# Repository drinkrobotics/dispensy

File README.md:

# Dispensy

One day aims to be a new hardware base for the [DrinkRobotics UbaBot](https://www.xythobuz.de/drinkrobotics.html).

Check out the [Dispensy documentation](https://drinkrobotics.github.io/dispensy/).

## License

This hardware of this project is licensed under the [CERN Open Hardware Licence Version 2 - Strongly Reciprocal (CERN-OHL-S-2.0+)](https://ohwr.org/cern_ohl_s_v2.txt) or any later version.
The SSD1306 footprint is from [KiCAD Rookie](https://kicadrookie.blogspot.com/2022/06/ssd1306-i2c-096in-oled-display-kicad_86.html).

The docs are built using [mdbook](https://github.com/rust-lang/mdBook), licensed as `MPL-2.0`.
The PCB SVG files in the documentation are displayed using [svg-pan-zoom](https://github.com/bumbu/svg-pan-zoom), licensed as `BSD-2-Clause`.
The 3D PCB files in the documentation are displayed using [three.js](hhttps://github.com/mrdoob/three.js), licensed as `MIT`.

Please also take a look at the `README.md` files in the subfolders of this project for more info.

     ------------------------------------------------------------------------------
    | Copyright (c) 2023 - 2024 Thomas Buck <thomas@xythobuz.de>                   |
    |                                                                              |
    | This source describes Open Hardware and is licensed under the CERN-OHL-S v2  |
    | or any later version.                                                        |
    |                                                                              |
    | You may redistribute and modify this source and make products using it under |
    | the terms of the CERN-OHL-S v2 (https://ohwr.org/cern_ohl_s_v2.txt)          |
    | or any later version.                                                        |
    |                                                                              |
    | This source is distributed WITHOUT ANY EXPRESS OR IMPLIED WARRANTY,          |
    | INCLUDING OF MERCHANTABILITY, SATISFACTORY QUALITY AND FITNESS FOR A         |
    | PARTICULAR PURPOSE. Please see the CERN-OHL-S v2 (or any later version)      |
    | for applicable conditions.                                                   |
    |                                                                              |
    | Source location: https://github.com/drinkrobotics/dispensy                   |
    |                                                                              |
    | As per CERN-OHL-S v2 section 4, should You produce hardware based on this    |
    | source, You must where practicable maintain the Source Location visible      |
    | on the external case of the Gizmo or other products you make using this      |
    | source.                                                                      |
     ------------------------------------------------------------------------------

The firmware of this project is licensed as GPLv3.
I initially adapted it from my own [Trackball](https://git.xythobuz.de/thomas/Trackball) and [Volcano Remote](https://git.xythobuz.de/thomas/sb-py) projects.
It uses the [Pi Pico SDK](https://github.com/raspberrypi/pico-sdk), licensed as BSD 3-clause, and therefore also [TinyUSB](https://github.com/hathach/tinyusb), licensed under the MIT license.
Some code is adapted from the TinyUSB examples.
To control the OLED display, [pico-ssd1306](https://github.com/daschr/pico-ssd1306) is used, licensed under the MIT license.
Repo metadata is embedded into the project using [cmake-git-version-tracking](https://github.com/andrew-hardin/cmake-git-version-tracking), licensed under the MIT license.

    This program is free software: you can redistribute it and/or modify
    it under the terms of the GNU General Public License as published by
    the Free Software Foundation, either version 3 of the License, or
    (at your option) any later version.

    This program is distributed in the hope that it will be useful,
    but WITHOUT ANY WARRANTY; without even the implied warranty of
    MERCHANTABILITY or FITNESS FOR A PARTICULAR PURPOSE.  See the
    GNU General Public License for more details.

    See <http://www.gnu.org/licenses/>.

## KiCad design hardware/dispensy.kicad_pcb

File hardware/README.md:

# Hardware

This is a KiCAD 8 hierarchical schematic and layout.
Take a look at the [docs](https://docs.kicad.org/7.0/en/eeschema/eeschema.html#hierarchical-schematics).

The repeated schematic sheets can also be replicated in the layout using [this plugin](https://github.com/MitjaNemec/ReplicateLayout).

To fetch symbols, footprints and 3d models automatically from [the JLCPCB parts library](https://jlcpcb.com/parts), [JLC2KiCad_lib](https://github.com/TousstNicolas/JLC2KiCad_lib) is used with the `fetch_jlc.sh` script.
To get the 3D models to have the correct offsets I used [this forked version](https://github.com/Xyntexx/JLC2KiCad_lib/tree/footprint_alignment_workarounds):

    pipx install git+https://github.com/Xyntexx/JLC2KiCad_lib.git@footprint_alignment_workarounds

In the future this may no longer be needed.

Gerber files and PDF and SVG plots can be generated using the included `generate_fab.sh` and `generate_plot.sh` scripts.

## External Libs

Uses SSD1306 footprint from [KiCAD Rookie](https://kicadrookie.blogspot.com/2022/06/ssd1306-i2c-096in-oled-display-kicad_86.html).

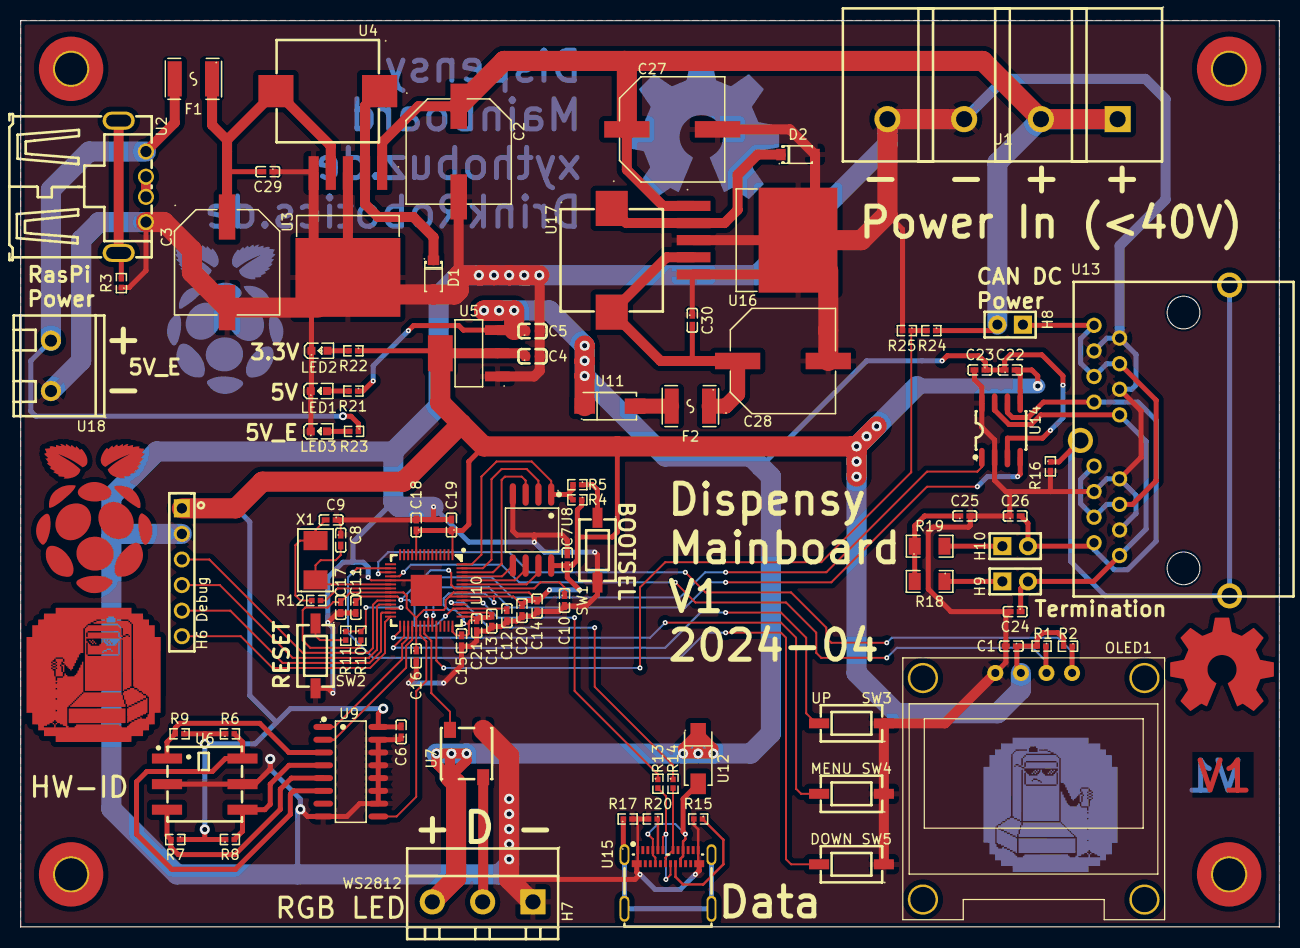
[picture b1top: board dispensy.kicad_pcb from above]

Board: 2 copper layers, 125.0 x 90.0 mm, 96 parts (0 on the bottom side), 64 nets.

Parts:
C1, C6, C7, C10, C11, C14, C15, C16, C17, C18, C19, C20, C21, C22, C29, C30: 100nF; C0402
C2, C27: 100uF; CAP-SMD_BD10.0-L10.3-W10.3-FD
C3, C28: 1000uF; CAP-SMD_BD10.0-L10.3-W10.3-LS11.3-FD
C4, C5: 10uF; C0603
C8, C9: 27p; C0402
C12, C13: 1uF; C0402
C23: 47nF; C0402
C24, C26: 100pF; C0402
C25: 4.7nF; C0402
D1, D2: MBR340F; SOD-123_L2.8-W1.8-LS3.7-RD
F1, F2: ASMD1812-350-16V; F1812
H6: Debug; HDR-TH_6P-P2.54-V-F
H7: WS2812; CONN-TH_XY300V-A-5.0-3P
H8: PWR; HDR-TH_2P-P2.54-V-M-1
H9: T_CH; HDR-TH_2P-P2.54-V-M-1
H10: T_CL; HDR-TH_2P-P2.54-V-M-1
H11, H12, H13, H14: MountingHole; MountingHole_3.2mm_M3_Pad_TopBottom
LED1, LED2, LED3: FC-D1608HGK-572C; LED0603-RD
OLED1: SSD1306; SSD1306_0.96_Oled
R1, R2, R4, R6, R7, R8, R9, R10, R25: 10K; R0402
R3, R16, R17: 1M; R0402
R5, R11, R12, R21, R22, R23: 1K; R0402
R13, R14: 27R4; R0402
R15, R20: 5K1; R0402
R18, R19: 60R4; R1206
R24: 147K; R0402
SW1: BOOTSEL; SW-SMD_L6.1-W3.6-LS6.6
SW2: RESET; SW-SMD_L6.1-W3.6-LS6.6
SW3: UP; SW-SMD_L6.1-W3.6-LS6.6
SW4: MENU; SW-SMD_L6.1-W3.6-LS6.6
SW5: DOWN; SW-SMD_L6.1-W3.6-LS6.6
U1: DBT50G-7_62-4P; CONN-TH_4P-P7.62_L15.2-W31.7-EX4.2
U2: USB-A; USB-A-TH_USB-302-T
U3, U16: LM2576S-5_0_TR; TO-263-5_L10.6-W9.6-P1.70-LS15.9-BR
U4, U17: 100uH; IND-SMD_L11.5-W10.0_YSPI1050
U5: AMS1117-3_3_C347222; SOT-223-4_L6.5-W3.5-P2.30-LS7.0-BR
U6: SKCR-16S; SW-SMD_SM_SKCR-16S
U7: WS2812E-V5; LED-SMD_4P-L5.0-W5.0-LS5.4-TL-1
U8: W25Q128JVSIQ; SOIC-8_L5.3-W5.3-P1.27-LS8.0-BL
U9: 74HC165D,653; SOIC-16_L9.9-W3.9-P1.27-LS6.0-BL
U10: RP2040; LQFN-56_L7.0-W7.0-P0.4-EP
U11, U12: SS54_C22452; SMA_L4.4-W2.8-LS5.4-R-RD
U13: CAN_IO; RJ45-TH_DS1129-05-S80BP-X
U14: TJA1042T_3_1J; SOIC-8_L5.0-W4.0-P1.27-LS6.0-BL
U15: USB-C; USB-C-SMD_TYPE-C-USB-18
U18: XY300V-A-5_0-2P; CONN-TH_XY300V-A-5.0-2P
X1: 12MHz; OSC-SMD_2P-L5.0-W3.2

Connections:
+1V1: C10.1, C11.1, C12.1, U10.23 (DVDD), U10.45 (VREG_VOUT), U10.50 (DVDD)
+3.3V: C1.1, C4.1, C6.2, C7.1, C13.1, C14.1, C15.1, C16.1, C17.1, C18.1, C19.1, C20.1, C21.1, C22.2, H6.1, OLED1.2 (VCC), R1.2, R2.2, R4.1, R6.1, R7.1, R8.1, R9.1, R10.2, R22.1, U5.2 (VOUT(TAB)), U5.4 (TAB), U8.8 (VCC), U9.16 (VCC), U10.1 (IOVDD), U10.10 (IOVDD), U10.22 (IOVDD), U10.33 (IOVDD), U10.42 (IOVDD), U10.43 (ADC_AVDD), U10.44 (VREG_IN), U10.48 (USB_VDD), U10.49 (IOVDD), U14.5 (VIO)
+5V: C5.1, C22.1, C23.1, H7.3, R21.1, U5.3 (VIN), U7.1 (VDD), U11.2 (K), U12.2 (K), U14.3 (VCC)
+VDC: C2.1, C27.1, H8.2, R24.1, U1.1, U1.2, U3.1 (VIN), U16.1 (VIN)
/EXT_PSU/Vout: C3.1, C29.2, F1.1, U3.4 (FB), U4.2
/PI/ADC0: R24.2, R25.1, U10.38 (GPIO26_ADC0)
/PI/Debug_Clock: H6.3, U10.24 (SWCLK)
/PI/Debug_Data: H6.4, U10.25 (SWD)
/PI/Debug_Rx: H6.6, U10.28 (GPIO17)
/PI/Debug_Tx: H6.5, U10.27 (GPIO16)
/PI/I2C_SCL: OLED1.3 (SCL), R1.1, U10.18 (GPIO15)
/PI/I2C_SDA: OLED1.4 (SDA), R2.1, U10.17 (GPIO14)
/PI/IO13: SW5.2, U10.16 (GPIO13)
/PI/IO14: SW4.2, U10.29 (GPIO18)
/PI/IO15: SW3.2, U10.30 (GPIO19)
/PI/LED_Din: U7.4 (DIN), U10.35 (GPIO23)
/PI/PI_PSU/Vout: C28.1, C30.2, F2.1, U16.4 (FB), U17.2
/PI/SPI_FLASH.SCLK: U8.6 (CLK), U10.52 (QSPI_SCLK)
/PI/SPI_FLASH.SD0: U8.5 (DI(IO0)), U10.53 (QSPI_SD0)
/PI/SPI_FLASH.SD1: U8.2 (DO(IO1)), U10.55 (QSPI_SD1)
/PI/SPI_FLASH.SD2: U8.3 (WP#(IO2)), U10.54 (QSPI_SD2)
/PI/SPI_FLASH.SD3: U8.7 (HOLD#orRESET#(IO3)), U10.51 (QSPI_SD3)
/PI/SPI_FLASH.SS: R4.2, R5.2, U8.1 (CS#), U10.56 (QSPI_SS)
/PI/SR_Clock: U9.2 (CP), U10.32 (GPIO21)
/PI/SR_Data: U9.9 (Q7), U10.34 (GPIO22)
/PI/SR_Load: U9.1 (PL#), U10.31 (GPIO20)
/PI/USBC.DM: R14.2, U15.A7 (D-), U15.B7 (D-)
/PI/USBC.DP: R13.2, U15.A6 (D+), U15.B6 (D+)
/PI/USBC.SHIELD: R17.1, U15.0
/PI/USBC.VBUS: U12.1 (A), U15.A4 (VBUS), U15.A9 (VBUS), U15.B4 (VBUS), U15.B9 (VBUS)
GND: C1.2, C2.2, C3.2, C4.2, C5.2, C6.1, C7.2, C8.1, C9.1, C10.2, C11.2, C12.2, C13.2, C14.2, C15.2, C16.2, C17.2, C18.2, C19.2, C20.2, C21.2, C23.2, C24.2, C25.2, C26.1, C27.2, C28.2, C29.1, C30.1, D1.2, D2.2, H6.2, H7.1, LED1.1 (-), LED2.1 (-), LED3.1 (-), OLED1.1 (GND), R3.1, R15.2, R16.2, R17.2, R20.2, R25.2, SW1.2, SW2.2, SW3.1, SW4.1, SW5.1, U1.3, U1.4, U2.4 (GND), U3.3 (GND), U3.5 (ON#/OFF), U3.6 (TAB), U5.1 (ADJ(GND)), U6.C1 (C), U6.C2 (C), U7.3 (GND), U8.4 (GND), U9.8 (GND), U9.10 (DS), U9.11 (D0), U9.12 (D1), U9.13 (D2), U9.14 (D3), U9.15 (CE#), U10.19 (TESTEN), U10.57 (GND), U13.3, U13.6, U13.7, U13.11, U13.14, U13.15, U14.2 (GND), U14.8 (STB), U15.A1 (GND), U15.A12 (GND), U15.B1 (GND), U15.B12 (GND), U16.3 (GND), U16.5 (ON#/OFF), U16.6 (TAB), U18.1
unnamed: C25.1, R18.2, R19.1
unnamed: H8.1, U13.4, U13.5, U13.8, U13.12, U13.13, U13.16
unnamed: H9.1, R18.1
unnamed: H10.1, R19.2
unnamed: LED1.2 (+), R21.2
unnamed: LED2.2 (+), R22.2
unnamed: LED3.2 (+), R23.2
unnamed: R5.1, SW1.1
unnamed: R11.2, SW2.1
unnamed: R16.1, U13.17, U13.18, U13.19
unnamed: U2.2 (D-), U2.3 (D+)
unnamed: R3.2, U2.5 (SH1), U2.6 (SH2)
unnamed: F1.2, R23.1, U2.1 (VCC), U18.2
unnamed: D1.1, U3.2 (OUT), U4.1
unnamed: H7.2, U7.2 (DO)
unnamed: R9.2, U6.1, U9.3 (D4)
unnamed: R8.2, U6.2, U9.4 (D5)
unnamed: R7.2, U6.4, U9.5 (D6)
unnamed: R6.2, U6.8, U9.6 (D7)
unnamed: U10.36 (GPIO24), U14.1 (TXD)
unnamed: U10.37 (GPIO25), U14.4 (RXD)
unnamed: R10.1, R11.1, U10.26 (RUN)
unnamed: R14.1, U10.46 (USB_DM)
unnamed: R13.1, U10.47 (USB_DP)
unnamed: C8.2, U10.20 (XIN), X1.1 (OSC1)
unnamed: R12.2, U10.21 (XOUT)
unnamed: F2.2, U11.1 (A)
unnamed: C24.1, H9.2, U13.1, U13.9, U14.7 (CANH)
unnamed: C26.2, H10.2, U13.2, U13.10, U14.6 (CANL)
unnamed: R20.1, U15.A5 (CC1)
unnamed: R15.1, U15.B5 (CC2)
unnamed: D2.1, U16.2 (OUT), U17.1
unnamed: C9.2, R12.1, X1.2 (OSC2)

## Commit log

2023-02-19 add imported jlc symbol and footprint libs
2023-02-19 work on pi schematic
2023-02-19 continue work on pi part
2023-02-20 more work on pi schematic
2023-02-20 put lm2576 in own schematic sheet
2024-01-10 remove jlc_lib from repo
2024-01-10 add descriptions for jlc part numbers
2024-01-10 add power connector on mainboard
2024-01-10 add readme
2024-01-10 short data lines on usb-a for powering external device
2024-01-10 start working on mainboard pcb layout
2024-01-12 More routing for power and can stuff
2024-01-13 start routing rp2040 stuff
2024-01-13 more routing
2024-01-13 add scripts
2024-01-13 replace 3.3v ldo with in-stock part
2024-01-14 add github pages docs with auto generated schematics and pcb layout
2024-01-14 fix master branch name in github workflow
2024-01-14 add missing parameter to docs script call in github actions workflow
2024-01-14 more routing of rp2040 power filtering
2024-01-20 first routing pass nearly done
2024-01-20 make svgs in docs interactive
2024-01-20 typo
2024-01-20 add CERN-OHL-S-2.0+ license
2024-01-21 add license header to source files
2024-01-21 more routing. all parts placed somewhere on board now.
2024-01-21 add screw connector for 5v-ext
2024-01-21 add resettable fuse to 5v ext output
2024-01-21 fuse for main 5v. parts moved and made dimensions smaller.
2024-01-21 more distance between mounting hole and power connector.
2024-01-21 generate pcb 3d files and visualize in docs
2024-01-21 fetch jlc parts in workflow
2024-01-21 install JLC2KiCad_lib in workflow
2024-01-21 install newer prusa-slicer in workflow
2024-01-21 appimages need fuse2 in workflow
2024-01-21 add libegl1 dep to workflow
2024-01-21 add links to generated docs pages
2024-01-21 tweak docs
2024-01-28 some more routing
2024-01-28 add power status leds
2024-01-28 route more power connections
2024-01-28 route more power lines
2024-01-28 add resistive divider for power in measurement. add buttons for display. remove gpio headers.
2024-01-28 some words in docs about mainboard
2024-02-02 bunch more routing of power and signals
2024-02-04 routing nearly finished
2024-02-04 clean up some routes
2024-02-05 try to fix scroll bug in docs svg viewer
2024-02-05 revision 1, date, tweak silkscreen
2024-02-05 improve usb c routing
2024-02-05 add some logos to pcb
2024-02-05 route remaining signals
2024-02-05 route some remaining power lines
2024-02-10 better marvin logo on pcb
2024-02-10 nearly done with routing
2024-03-04 route more gnd
2024-03-08 nearly done with routing, one track missing
2024-03-08 no unrouted tracks left
2024-03-08 add ground planes
2024-03-12 tweak some routes
2024-03-12 generate separate front and back layouts for docs
2024-04-05 convert to kicad 8 and run drc
2024-04-05 use new 3d rendering in docs
2024-04-05 kicad 8 for gh actions workflow
2024-04-05 replace rgb led connector with screw terminal
2024-04-05 populate and visualize oled as 4pin header
2024-04-05 replace 1000uF capacitor with in stock part
2024-04-05 replace usb a with in stock part
2024-04-16 start work on firmware
2024-04-16 fix path in cmake gh action
2024-04-16 clean up firmware skeleton
2024-04-16 draw version and repo info on oled
2024-04-16 detect if OLED is plugged in
2024-04-16 add hw id read

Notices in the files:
hardware/dispensy.kicad_pcb:
Licensed under the CERN-OHL-S-2.0+
